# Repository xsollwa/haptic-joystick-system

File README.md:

# haptic-joystick-system
A handheld controller that uses air pressure to send haptic feedback.

**Created by:** Ruzanna Gaboyan and Philip Golczak

**Date:** June 7, 2025

## Overview

The **Haptic Joystick System** is a *wireless controller that lets you wirelessly control robot arms in XYR directions* using your hand movement and pressure. It includes a two dual axis joystick modules for motion control in XYR directions, and a small squeezable air bulb that sends and receives air pressure signals. The controller *reads how hard you're squeezing using an air pressure sensor and can also send pressure back* into the bulb to communicate resistance.

**Why we made it**: By this project we wanted to make controlling robots more natural by *"feeling what they feel"* in addition to just moving them. This is useful especially in robotics tasks where pressure precision applied by the robot matters: like gripping and squeezing fragile objects. 

//////Note: we removed the screen feature to bring the cost of the project down.

## Features
- **Pneumatic haptic feedback system:** Squeeze a small air bulb to send signals to a robot arm.
- **Joystick control**: Move the robot arm in XYR *(R-Rotation)* directions.
- **Two-way haptic feedback communication:** Air pumping piston mechanism also sends pressure back into the bulb when robot grips something.
- **Wireless communication:** ESP32 hamdles communication between the controller and the robot over Wi-Fi.
- **Custom PCB and 3D case:** Designed and built from scratch for this project.
- **OLED Display:** A little screen shows live data like grip pressure, feedback intensity and other info.
- **Ergonomic handle options:** In addition to the default casing, we CAD-ed an alternate ergonomic grip design for more comfort that can be added on the controller.

Ergonomic handle options: In addition to the default casing, we CAD-modeled an alternate ergonomic grip design for added comfort and modularity when holding the controller.

### Materials and Budget

## Bill of Materials

| Part Number | Part Name           | Description                                      | Unit Price | Total Price | Link |
|-------------|---------------------|--------------------------------------------------|------------|-------------|------|
| MP1         | ESP32               | Wi-Fi Microprocessor                             | $5.99      | $5.99       | [Amazon](https://www.amazon.com/gp/product/B0DDPJQX3X/ref=ox_sc_act_image_11?smid=A1VTL661FOEJB1&th=1) |
| J1, J2      | Joystick Module (2x)| KY-023 control joystick module                   | $6.79      | $6.79       | [Amazon](https://www.amazon.com/Joystick-Sensor-Module-Controller-KY-023/dp/B08681KFSD/) |
| S1          | AITRIP Pressure Sensor | Barometric Pressure Sensor Module              | $9.99      | $9.99       | [Amazon](https://www.amazon.com/AITRIP-Pressure-Digital-Barometric-Controller/dp/B09KXXBCYX/) |
| PCB1        | PCB                 | Fabricated PCB                                   | $5.00      | $5.00       | [PCBWay](https://pcbway.com/) |
| BT1         | Battery Connector   | Plug in for LiPo battery                         | $3.77      | $3.77       | [Amazon](https://www.amazon.com/gp/product/B0DY5GRSQW/ref=ox_sc_act_title_7?smid=AH55IWDCGXER3&psc=1) |
| BULB        | Pipet bulb          | 4ml Air bulb for pressure sensor                 | $7.98      | $7.98       | [Amazon](https://www.amazon.com/gp/product/B01LZHMLQA/ref=ox_sc_act_title_6?smid=A29JIFH4ZXPNL8&psc=1) |
| TUBE        | Tubes               | Tube to connect the sensor, pump and air bulb    | $7.49      | $7.49       | [Amazon](https://www.amazon.com/uxcell-Silicone-Tubing-Rubber-Transfer/dp/B085N17TDB/) |
| CN1         | Tube T-Connectors   | Connectors for the tube, air bulb, sensor, pump | $11.99     | $11.99      | [Amazon](https://www.amazon.com/gp/product/B06XGCM2RX/ref=ox_sc_act_title_5?smid=A1THAZDOWP300U&psc=1) |
| SYRINGE     | Syringe             | 10ml Syringe for inflating and deflating         | $5.99      | $5.99       | [Amazon](https://www.amazon.com/Plastic-Syringe-Measurement-Scientific-Measuring/dp/B09MYPTD1P/) |
| AT1         | Actuator            | Mini Linear Actuator to push air                 | $19.99     | $19.99      | [Amazon](https://www.amazon.com/Actuator-Electric-Actuators-Robotics-Automation/dp/B0D17H1HGV/) |
| MD1         | Motor Driver        | Stepper Motor Driver Module                      | $6.98      | $6.98       | [Amazon](https://www.amazon.com/WWZMDiB-L298N-H-Bridge-Controller-Raspberry/dp/B0CR6BX5QL/) |
| **TOT**     | **Total (excl. taxes & shipping)** |                                              |            | **$91.96**  |      |
|             | **Total WITH taxes & shipping**   |                                              |            | **$114.50** |      |

## Notes on Purchasing and Shipping

We want to purchase most of the parts from Amazon. We chose Amazon as our primary supplier because we have access to Amazon Prime, which has faster shipping. The prime shipping makes the packs cheaper than the singular alternatives at other sources (like AliExpress). Also, we own some of the parts, like the battery and boost converter, so their cost is put as $0. 

//Note: The difference between Aliexpress sourcing and Amazon sourcing for this project is ~$7.00

## How it Works
1) Joystick modules send movement data wirelessly through ESP32 to the robot arm,
2) When you squeeze the air bulb the pressure sensor reads the force,
3) ESP32 sends that signal to the robot (like our [Remote Assist Hand](https://github.com/xsollwa/remote-assist-hand), but the controller can potentially be used on other robots as well),
4) If the robot grips something, it sends resistance signals back,
5) Air pumping mechanism activates and sends pressure into the bulb,
6) You feel it!
7) OLED screen displays pressure data, joystick values, connection status and more. Pressing either joystick down switched between display modes.

## Pictures 
**PCB**

**3D model**

<p align="center">
  
  <br>
  
  <br>
  
</p>

## Building Process
1) Brainstorming and sketches
2) PCB design in KiCAD
3) CAD modeling in OnShape
4) Coding
5) Revision and Optimization
6) Assembly and testing

## Journal
Our full development journal can be found [here](./JOURNAL.md)

## Contact
For any questions or suggestions please reach out to us at *gaboyanruzanna@gmail.com* or *ph.golczak@gmail.com* .

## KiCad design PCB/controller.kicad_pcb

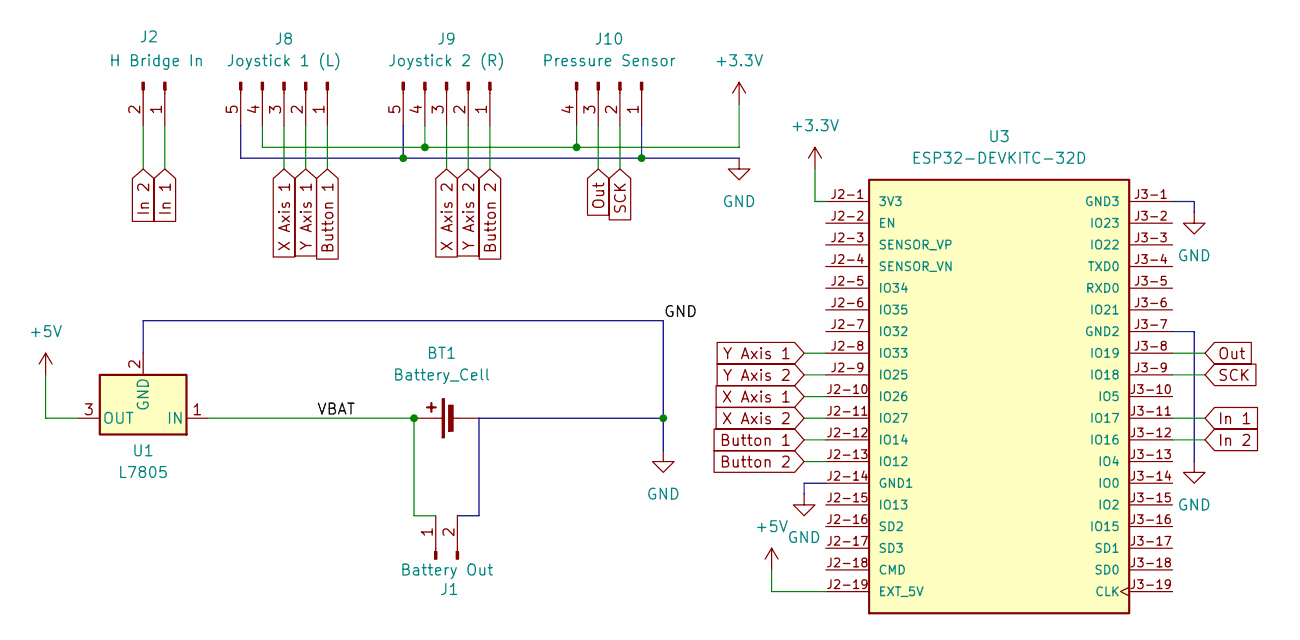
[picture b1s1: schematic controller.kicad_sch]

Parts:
BT1: Battery_Cell; Battery Connector
J1: Battery Out; Battery Connector
J2: H Bridge In; PinHeader_1x02_P2.54mm_Vertical
J8: Joystick 1 (L); PinHeader_1x05_P2.54mm_Vertical
J9: Joystick 2 (R); PinHeader_1x05_P2.54mm_Vertical
J10: Pressure Sensor; PinHeader_1x04_P2.54mm_Vertical
U1: L7805; TO-220-3_Vertical
U3: ESP32-DEVKITC-32D; ESP32; PARTREV V4

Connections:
+3.3V: J8.4, J9.4, J10.4, U3.J2-1 (3V3)
+5V: U1.3 (OUT), U3.J2-19 (EXT_5V)
/VBAT: BT1.1 (+), J1.1, U1.1 (IN)
Button 1: J8.1, U3.J2-12 (IO14)
Button 2: J9.1, U3.J2-13 (IO12)
GND: BT1.2 (-), J1.2, J8.5, J9.5, J10.1, U1.2 (GND), U3.J2-14 (GND1), U3.J3-1 (GND3), U3.J3-7 (GND2)
In 1: J2.1, U3.J3-11 (IO17)
In 2: J2.2, U3.J3-12 (IO16)
Out: J10.3, U3.J3-8 (IO19)
SCK: J10.2, U3.J3-9 (IO18)
X Axis 1: J8.3, U3.J2-10 (IO26)
X Axis 2: J9.3, U3.J2-11 (IO27)
Y Axis 1: J8.2, U3.J2-8 (IO33)
Y Axis 2: J9.2, U3.J2-9 (IO25)

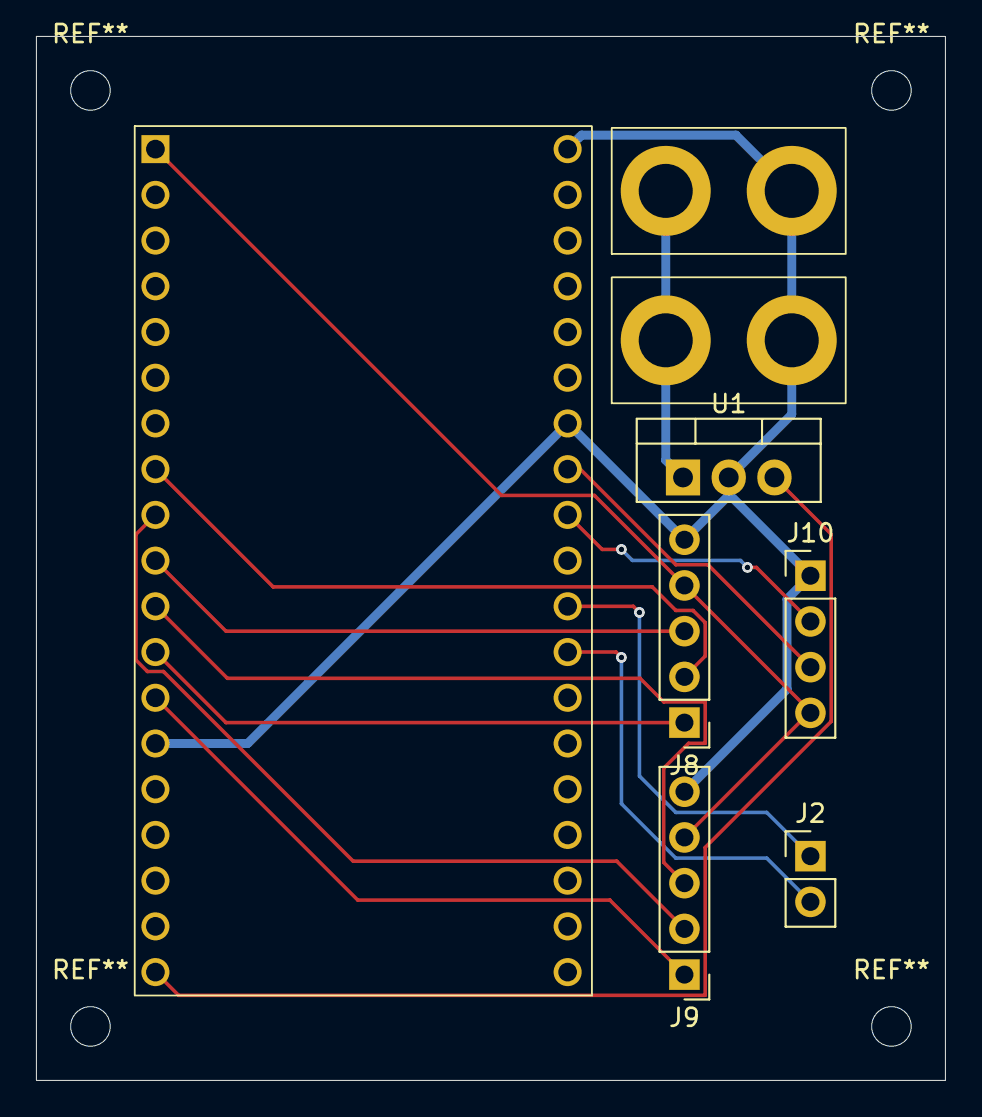
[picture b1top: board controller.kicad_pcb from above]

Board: 2 copper layers, 50.5 x 58.0 mm, 8 parts (0 on the bottom side), 14 nets.

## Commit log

2025-06-07 Create MATERIALS-AND-BUDGET
2025-06-13 Update JOURNAL.md (June 11-12)
2025-06-13 Update MATERIALS-AND-BUDGET
2025-06-16 Update README.md (June 15)
2025-06-16 Create file
2025-06-16 Rename PCB/file to PCB/backups/file
2025-06-16 Rename Screenshot 2025-06-13 144023.png to pcb.png
2025-06-16 Rename Screenshot 2025-06-13 162339.png to 3d.png
2025-06-16 Rename Screenshot 2025-06-13 144101.png to schematic.png
2025-07-01 Update JOURNAL.md (June 29 Ruzanna
2025-07-01 Update JOURNAL.md (June 28)
2025-07-04 Created Code Folder (July 3)
2025-07-04 Updated Code (July 3)
2025-07-06 Rename Controller Assembly.step to CAD/Controller Assembly.step
2025-07-06 Rename CAD/Screenshot 2025-07-05 223224.png to CAD/images/back.png
2025-07-06 Rename Screenshot 2025-07-05 223244.png to front.png
2025-07-06 Rename Screenshot 2025-07-05 223329.png to back-with-lid.png
2025-07-06 Rename Controller Lid.step to Production/Controller Lid.step
2025-07-06 Updated PCB and Production Folders (July 6)
2025-07-06 Updated JOURNAL.md (July 6)
2025-07-06 Update README.md (Final!)
2025-07-06 Update JOURNAL.md added total time
2025-07-06 Update and rename Bill of Materials (BOM) controller - Лист1 (2).csv to Bill of Materials (BOM)
2025-07-19 add oled screen + screen switching using joystick buttons
2025-07-23 Updated PCB and CAD (July 22)
2025-07-23 Updated JOURNAL.md (July 22)
2025-07-24 Updated BOM.csv (July 24)
